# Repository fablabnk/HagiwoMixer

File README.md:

The repo contains the KiCad files for manufacturing the printed circuit board and front panel for a 4-channel Eurorack active mixer, based on the one Hagiwo assembled by hand [here](https://note.com/solder_state/n/nffc1a33053be). This project is a simpler precursor to building a Eurorack module with a Daisy Seed, in order to hone my skills and go one-time through the PCB manufacture process.

# Still to pay attention to! (A.K.A. the TODO list) 

- PROBLEM: it's the main board not the panel that needs to be mirrored - how to do this? See [here](https://www.reddit.com/r/KiCad/comments/sazql5/is_there_a_mirror_tool_for_flipping_the_pcb_layout/)
- do the connections on my pots go downwards onto the board?
- the thonkiconn screws should also how 
- component heights should be such that they all poke through the front panel at the same height (check with 3D model)
- Note: our screw holes on the panel template are not perfectly placed! complete the mounting holes section in the table below

# Aims / Design Constraints

For this design I am aiming to:
- use through-hole components only
- mount the pots and jacks directly onto the PCB
    - as opposed to just securing them to the panel and wiring each individually to the board (as in the original Hagiwo design)
- place all component on a single board (no stacking)
    - this will limit the number of inputs to 4 (instead of Higawo's 5)
- also design the module front panel as a PCB and have it manufactured at the same time

# Components / Bill of Materials (BOM)

- 4 x [10K potentiometers Alpha 9mm (inputs)](https://www.musikding.de/Alpha-Pot-9mm-10k-lin-dual-concentric)  
- 1 x [100K potentiometer Alpha 9mm (output)](https://www.musikding.de/Alpha-Pot-9mm-100k-lin-dual-concentric)
- 6 x [Thonkiconn 3.5mm jack sockets](https://www.thonk.co.uk/shop/thonkiconn/)  
- 1 x [TL072 dual op-amp (integrated circuit in PDIP package)](https://www.ti.com/product/TL072#design-development)  
- 1 x [2x5 Pin Shrouded Header (Eurorack power connector)](https://oddvolt.com/products/shrouded-10pin-eurorack-power-header)  
- 5 x 100K resistors
- 1 x 22K resistor
- 1 x 4.7K resistor
- 1 x 1K resistor
- 2 x 4.7uF electrolytic capacitors (block out high-frequency AC noise or ripple that might be present on the DC power supply line.)

# Workflow

1. [Design the schematic](#1-design-the-schematic)
2. [Simulate the circuit (TODO)](#2-simulate-the-circuit-todo)
3. [Design Eurorack board templates](#3-design-eurorack-board-templates)
4. [Assign footprints and place components](#4-assign-footprints-and-place-components)
5. [Route traces](#5-route-traces)
6. [Design the front panel](#6-design-the-front-panel)
7. [Produce gerber files](#7-produce-gerber-files)
8. [Send to manufacturer (TODO)](#8-send-to-manufacturer-todo)

# 1. Design the schematic

I am following [Hagiwo's](https://note.com/solder_state/n/n54e016f19c94) hand draw schematic, as referenced here:

The [Doepfer schematic](https://www.doepfer.de/DIY/mixer.gif) detailed on [this page](https://www.doepfer.de/DIY/a100_diy.htm) is also useful for comparison, but includes some extra details and differences.

## How the mixer works

To understand the schematic, I found it helped to describe it briefly in terms of signal flow:
1. We attentuate the incoming signal from each jack input using a potentiometer
2. The signals are then mixed together and fed to the input of an operational amplifier
3. The op amp attentuates the signal by a fixed level (to compensate for the volume increase of the combined inputs)
4. A potentiometer across second op amp acts as a master volume, attentuating the mixed signals
5. The attentuated output goes to the jack output

## Jacks

I'm using `AudioJack2_SwitchT` as the jack symbol on the schematic. It has only tip and sleeve, where:
- the tip is the "hot" pin which should carry the audio signal to the potentiometer input
- the sleeve goes to ground

## Power

Designing the mixer helped me get to grips with how to supply power to a module from a Eurorack power supply.

Key points:
- Power comes in via a 10-pin shrouded power header
    - Shrouded means that the cable can only be inserted one way
    - The symbol for this can be found in the [eurocad library](https://github.com/nebs/eurocad) under the name `EURO_PWR_2x5`
    - From the 10 pins it is [standard practice](https://pichenettes.github.io/mutable-instruments-documentation/modules/plaits/downloads/plaits_v50.pdf) to short together:
        - the two +12v rails
        - the two -12v rails
        - the six ground pins
- The +-12V rails are used to power our TL072 dual op-amp chip
    - When placing the TL072 dual op-amp schematic symbol, we must click three times
        - twice for each individual op amp
        - once for the power part of schematic
- 2 x 4.7uF electrolytic capacitors are used between the +12V and -12V rails and ground
    - their purpose is to smooth out unexpected small fluctuations in voltage

- some useful principles of voltage control and power in Eurorack are also covered [here](https://doepfer.de/a100_man/a100t_e.htm)

# 2. Simulate the circuit (TODO)

The aim here is to check that the signals meet Eurorack output levels

Key points:
- we will use Spice simulation
- [advice](https://www.reddit.com/r/KiCad/comments/1961s6p/using_the_spice_simulator_in_kicad_on_a_guitar/) is to replace potentiometers with fixed value resistors and vary the values between simulation passes
    - So check for a given input that we get an expected output
    - But what inputs to use?
- the schematic needs to be reworked to be suitable for a PSPICE simulation (It isn't as simple as "hit run, get a waveform.")
- AC Sweep is probably the analysis method to use

# 3. Design Eurorack board templates

I found it important to first design superimposed templates for both the front panel and main PCB. This is because the holes in the front panel template will be derived directly from the centre hole positions of the jacks and pots on the main board.

My starting point was this repo of [Euroack KiCad project templates](https://github.com/clacktronics/Eurorack_KiCAD_templates). Unfortunately, there was no 6HP template, so I used the opportunity to design my own.

The width of Eurorack modules is measured in HP (Horizontal Pitch), where one unit of HP is 5.08mm wide (0.2 of a an inch). Fortunately our KiCad grid already has a setting for this.

I started by defining three templates, using the original [Doepfer specifications](https://www.doepfer.de/a100_man/a100m_e.htm). This [online converter](https://gcoulby.github.io/Eurorack-Unit-HP-Converter/) was also useful.

## 1. Front panel template
- this is the exact 6HP width and normal height i.e. 30.48mm x 128.5mm
- it is helpful to keep everything on a HP grid
- i used a dotted outline and placed it on the User Drawings layer, as it won't be used for manufacture

## 2. Front panel itself
- this is 0.24mm narrower either side and the same height i.e. 30.00mm x 128.50mm
- it also includes two oval screw mounting holes (enough for modules < 12HP):
    - the horizontal centre of which should be 1HP in from the edge
    - the vertical centre of which should be 3mm from the edge
    - diameter should be 3.2mm
    - width of the oval should be 5.2mm
- I placed it on the Edge Cuts layer, as it represents the milled board outline

## 3. Main board
- this is 0.5mm narrower still either side than the front panel and not as tall i.e. 29.00m x 106mm
- the reduction in height is necessary so that the board passes the mounting rails
- I placed it on the Edge Cuts layer, as it represents the milled board outline

In KiCad, rectangles are specified using x and y start and end points. Here are points for all the elements mentioned above:

| Item                | X Start    | X End       | Y Start   | Y End       |
|---------------------|------------|-------------|-----------|-------------|
| Front Panel Template| 0          | 30.48       | 0         | 128.5       |
| Front Panel         | 0.24       | 30.24       | 0         | 128.5       |
#| Mounting Hole 1     | 5.08 - 2.6 | 5.08 + 2.6  | 3.2 - 1.5 | 3.2 + 1.5   |
#| Mounting Hole 2     | 5.08 - 2.6 | 5.08 + 2.6  | 3.2 - 1.5 | 3.2 + 1.5   |
| Main Board          | 0.74       | 29.74       | 11.25     | 117.25      |

Once all three templates were complete, I grouped them all together to ensure they are not accidentally moved out of position relative to one another. It is also possible to snap different elements within the design to grid points, to aid relative placement of components.

# 4. Assign footprints and place components

## Assign Footprints

Before the components can be laid out on the PCB, a footprint for each must be given in the schematic. Below are the footprints I used for some key components, some of of which are taken from the [eurocad library](https://github.com/nebs/eurocad)

| Component Name         | Footprint Name                |
|------------------------|-------------------------------|
| 3.5mm Jack Sockets     | eurocad:PJ301M-12_T_S        |
| Potentiometers         | eurocad:Alpha9mmPot          |
| TL072 Dual Op Amp      | Package_DIP:DIP-8_W7.62mm    |
| Shrouded Power Header  | Connector_IDC:IDC-Header_2x05_P2.54mm_Vertical |

## Placing Components

There are tools available purely for doing front panel design, such as [Front Panel Designer](https://www.frontpanelexpress.com/front-panel-designer) and [Synth Panels Designer](https://cdm.link/2020/07/synth-panels-designer-makes-diy-panels-free/). These could help to define the ideal component placement in future,but this time round I just placed by hand using the main board height as the core constraint.

Key points:
- Placement was done within the bounds of the main board template
- The height of the board (106mm) limits the design to five rows of jack potentiometer pairs in total
- If the components were not mounted on the board directly
    - an extra row could be squeezed in
    - or the existing rows could be better spaced 
- I followed this simple design constraint:
    - For input rows: Jacks on the left, pots on the right
    - For output row: Jack on the right, pot on the left
- The jack and potentiometer pairs were placed at equal vertical distance from one another
    - The KiCad measurement tool came in handy to check this
- The remaining components were placed in the spaces between the pairs, and the power connector at the bottom

# 5. Route traces

Key points:
- We use only two layers (front and back)
- The PCB component holes are 'vias' which allow the traces to be routed between the two layers
- I followed a simple 'ground plane' convention to decide which traces to put on which of the layers, which states that all connections that go to ground should be on one side of the board (the back) and all other connections on the other side (the front)
- I used thicker traces of 0.5mm for the power traces leading from the power header to the capacitors and op amp. This I had seen recommended in other designs.
- For all other traces I used the default thickness of 0.25mm

# 6. Design the front panel

Designing the front panel was a simple matter of:
1. Creating mounting holes whose centre points match those of the circles on the jack and pot footprints
2. Moving the panel template, plus mounting holes to one side (still on the grid)
3. Adding text, row markers and logos as drawings to the silkscreen layer
4. Mirroring the design at the end, so that the silk screening is visible when we flip the panel over to place it on top of the pot/jack shafts

Key points:
- To make the mounting holes, I oriented the grid so that the centre of the existing components was directly on a grid boundary
- The diamater of the mounting holes was as follows
    - Alpha 9mm pots: 7mm
    - Thonkiconn jacks: 6mm
- To make the holes, use the "Add a footprint" icon and select searching for `MountingHole`
    - Unlike plain circles, this makes sure they actually get included in the Gerber drill files
    - Note: Mounting hole footprints are measured in radius, not diameter, so I used 3.5mm and 3mm variants
- For cooler visual effects, it is also possible to draw on the solder mask layer or experiment with surface finishes (e.g. ENIG vs HASL)

# 7. Produce Gerber files

Once all the above has been done, we can temporarily delete the front panel elements to produce the PCB Gerber files and vice versa.

Key points:
- Go to `File Menu -> Plot` to start the export process for each board
    - Click `Generate Drill Files` - this should create a set of .drl files
    - Then click `Plot` - this should create a .gbr file for each KiCad layer
- Both the drill and Gerber files can (and should!) be checked in KiCad's inbuilt Gerber viewer. Just double click on the new project files that have appeared
- You may need to copy out the first set of .gbr and .drl files before producing the second.

# 8. Send to manufacturer (TODO)

To be decided...

## Links
TL072 sheet:  
https://www.ti.com/product/TL072#design-development  
Nice video explaining op amps configurations:  
https://youtu.be/_HHxV-7alwE?si=UBo3YyZvg435RTeY  
and the blog post with schematics and explanation about op amps:  
https://dronebotworkshop.com/op-amps/

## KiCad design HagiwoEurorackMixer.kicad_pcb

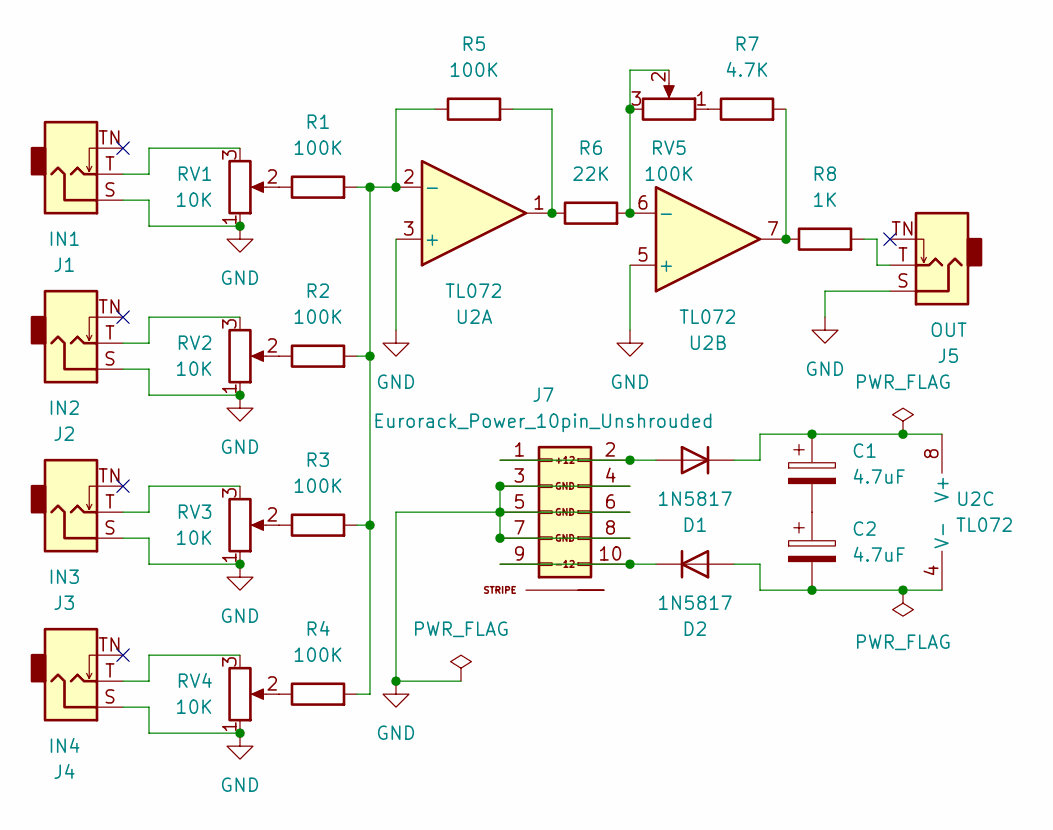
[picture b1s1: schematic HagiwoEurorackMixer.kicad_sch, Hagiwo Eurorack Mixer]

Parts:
C1, C2: 4.7uF; CP_Radial_D5.0mm_P2.50mm
D1, D2: 1N5817; D_DO-41_SOD81_P10.16mm_Horizontal
J1: IN1; EighthInch_PJ398SM_T_TN_S
J2: IN2; EighthInch_PJ398SM_T_TN_S
J3: IN3; EighthInch_PJ398SM_T_TN_S
J4: IN4; EighthInch_PJ398SM_T_TN_S
J5: OUT; EighthInch_PJ398SM_T_TN_S
J7: Eurorack_Power_10pin_Unshrouded; IDC-Header_2x05_P2.54mm_Vertical_Euro_Power_Striped; Part Number 1-1002FBV0T
R1, R2, R3, R4, R5: 100K; R_Axial_DIN0207_L6.3mm_D2.5mm_P7.62mm_Horizontal
R6: 22K; R_Axial_DIN0207_L6.3mm_D2.5mm_P7.62mm_Horizontal
R7: 4.7K; R_Axial_DIN0207_L6.3mm_D2.5mm_P7.62mm_Horizontal
R8: 1K; R_Axial_DIN0207_L6.3mm_D2.5mm_P7.62mm_Horizontal
RV1, RV2, RV3, RV4: 10K; Pot_9mm_DShaft_RemovedPins4_5
RV5: 100K; Pot_9mm_DShaft_RemovedPins4_5
U2: TL072; DIP-8_W7.62mm

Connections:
GND: J1.S, J2.S, J3.S, J4.S, J5.S, J7.3 (GND), J7.4 (GND), J7.5 (GND), J7.6 (GND), J7.7 (GND), J7.8 (GND), RV1.1, RV2.1, RV3.1, RV4.1, U2.3 (+), U2.5 (+)
unnamed: C1.2, C2.1
unnamed: D1.2 (A), J7.1 (+12V), J7.2 (+12V)
unnamed: C1.1, D1.1 (K), U2.8 (V+)
unnamed: C2.2, D2.2 (A), U2.4 (V-)
unnamed: D2.1 (K), J7.9 (-12V), J7.10 (-12V)
unnamed: J1.T, RV1.3
unnamed: J2.T, RV2.3
unnamed: J3.T, RV3.3
unnamed: J4.T, RV4.3
unnamed: J5.T, R8.2
unnamed: R1.1, RV1.2
unnamed: R2.1, RV2.2
unnamed: R3.1, RV3.2
unnamed: R4.1, RV4.2
unnamed: R5.2, R6.1, U2.1
unnamed: R7.1, RV5.1
unnamed: R7.2, R8.1, U2.7
unnamed: R1.2, R2.2, R3.2, R4.2, R5.1, U2.2 (-)
unnamed: R6.2, RV5.2, RV5.3, U2.6 (-)

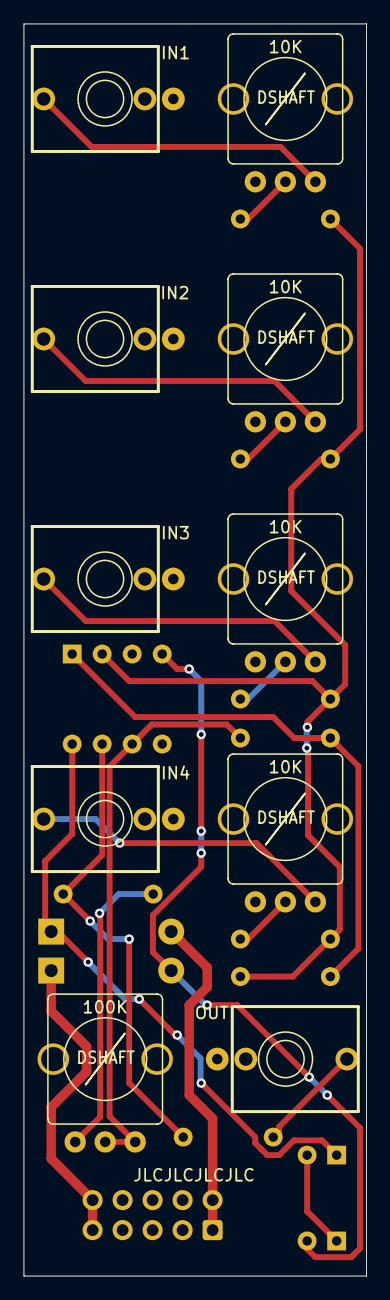
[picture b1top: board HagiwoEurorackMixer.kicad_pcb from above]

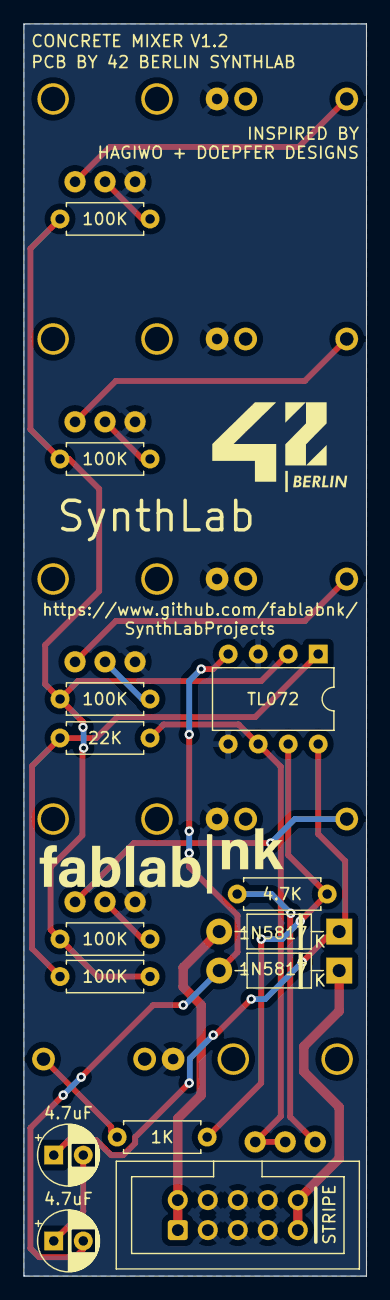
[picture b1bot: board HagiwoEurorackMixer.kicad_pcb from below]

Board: 2 copper layers, 29.0 x 106.0 mm, 24 parts (14 on the bottom side), 20 nets.

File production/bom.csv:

Designator,Footprint,Quantity,Value,LCSC Part #
"C1, C2",CP_Radial_D5.0mm_P2.50mm,2,4.7uF,
"D1, D2",D_DO-41_SOD81_P10.16mm_Horizontal,2,1N5817,
J1,EighthInch_PJ398SM_T_TN_S,1,IN1,
J2,EighthInch_PJ398SM_T_TN_S,1,IN2,
J3,EighthInch_PJ398SM_T_TN_S,1,IN3,
J4,EighthInch_PJ398SM_T_TN_S,1,IN4,
J5,EighthInch_PJ398SM_T_TN_S,1,OUT,
J7,IDC-Header_2x05_P2.54mm_Vertical_Euro_Power_Striped,1,Eurorack_Power_10pin_Unshrouded,
"R1, R2, R3, R4, R5",R_Axial_DIN0207_L6.3mm_D2.5mm_P7.62mm_Horizontal,5,100K,
R6,R_Axial_DIN0207_L6.3mm_D2.5mm_P7.62mm_Horizontal,1,22K,
R7,R_Axial_DIN0207_L6.3mm_D2.5mm_P7.62mm_Horizontal,1,4.7K,
R8,R_Axial_DIN0207_L6.3mm_D2.5mm_P7.62mm_Horizontal,1,1K,
"RV1, RV2, RV3, RV4",Pot_9mm_DShaft_RemovedPins4_5,4,10K,
RV5,Pot_9mm_DShaft_RemovedPins4_5,1,100K,
U2,DIP-8_W7.62mm,1,TL072,

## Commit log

2024-04-01 completed v1 of README. mounting holes still to do on front panel
2024-04-03 update:
2024-04-04 main board needs mirroring
2024-04-04 updated readme with mirroring issue
2024-04-05 mirrored version of PCB completed
2024-04-05 renamed project from Higawo to Hagiwo and pruned all but the most necessary project files
2024-04-11 Produced gerber files for test laser cutting - adapted all panel drill holes to 6mm
2024-04-11 Produced separate front panel and PCB gerber files for manufacture
2024-04-12 Produced files for uploading to jlcpcb - first attempt
2024-04-12 updated gerber files to include back solder mask layers - as requested by JCLPCB
2024-05-16 pushing latest version
2024-07-12 v1.1 complete - fixed power header orientation, implemented ground plane, equal horizontal spacing from board edge for pots and jacks, flipped some components to back and reoriented, rerouted, redesi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
2024-07-12 removed need for KiCad subfolder - all project files now in root
2024-08-13 latest updates
2025-01-11 laid out V1.1 again for better placement
2025-01-11 moved decoupling caps back near power rails - now really ready for V1.1 production
2025-01-11 realised pots and jacks were mirrored horizontally across the whole pcb - reworked and rerouted still for V1.1 - with production files
2025-01-12 experimenting with ibom as github pages index.html
2025-02-12 adding lasercut ready template
2025-02-24 v1.2 ready for production - slightly unsure if volume pot left/right side wiring is correct
